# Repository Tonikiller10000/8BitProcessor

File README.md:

# 8Bit Computer

### Description:
This is a series of modules(3 at the moment) witch make an functional 8 bit processor for educational purposes: 
- [ALU](https://github.com/Tonikiller10000/8BitProcessor/tree/main/Processor_ALU_V1.0)
- [Display Register](https://github.com/Tonikiller10000/8BitProcessor/tree/main/DisplayRegister)
- [CLK Pulse Generator](https://github.com/Tonikiller10000/8BitProcessor/tree/main/ClkPulseGenerator)

> [!TIP]
> By clicking on a module link, you can read it\`s speciffic documentation.

<table>
  <tr>
    <td>ALU</td>
    <td>Display Register</td>
    <td>CLK Pulse Generator</td>
  </tr>
  <tr>
    <td></td>
    <td></td>
    <td></td>
  </tr>
 </table>

Links:
BenEater YouTube: https://www.youtube.com/beneater 
BenEater WebSite: https://eater.net/8bit   
GitHub: https://github.com/Tonikiller10000/8BitProcessor 
JLC: https://jlcpcb.com/ 

Photo:....

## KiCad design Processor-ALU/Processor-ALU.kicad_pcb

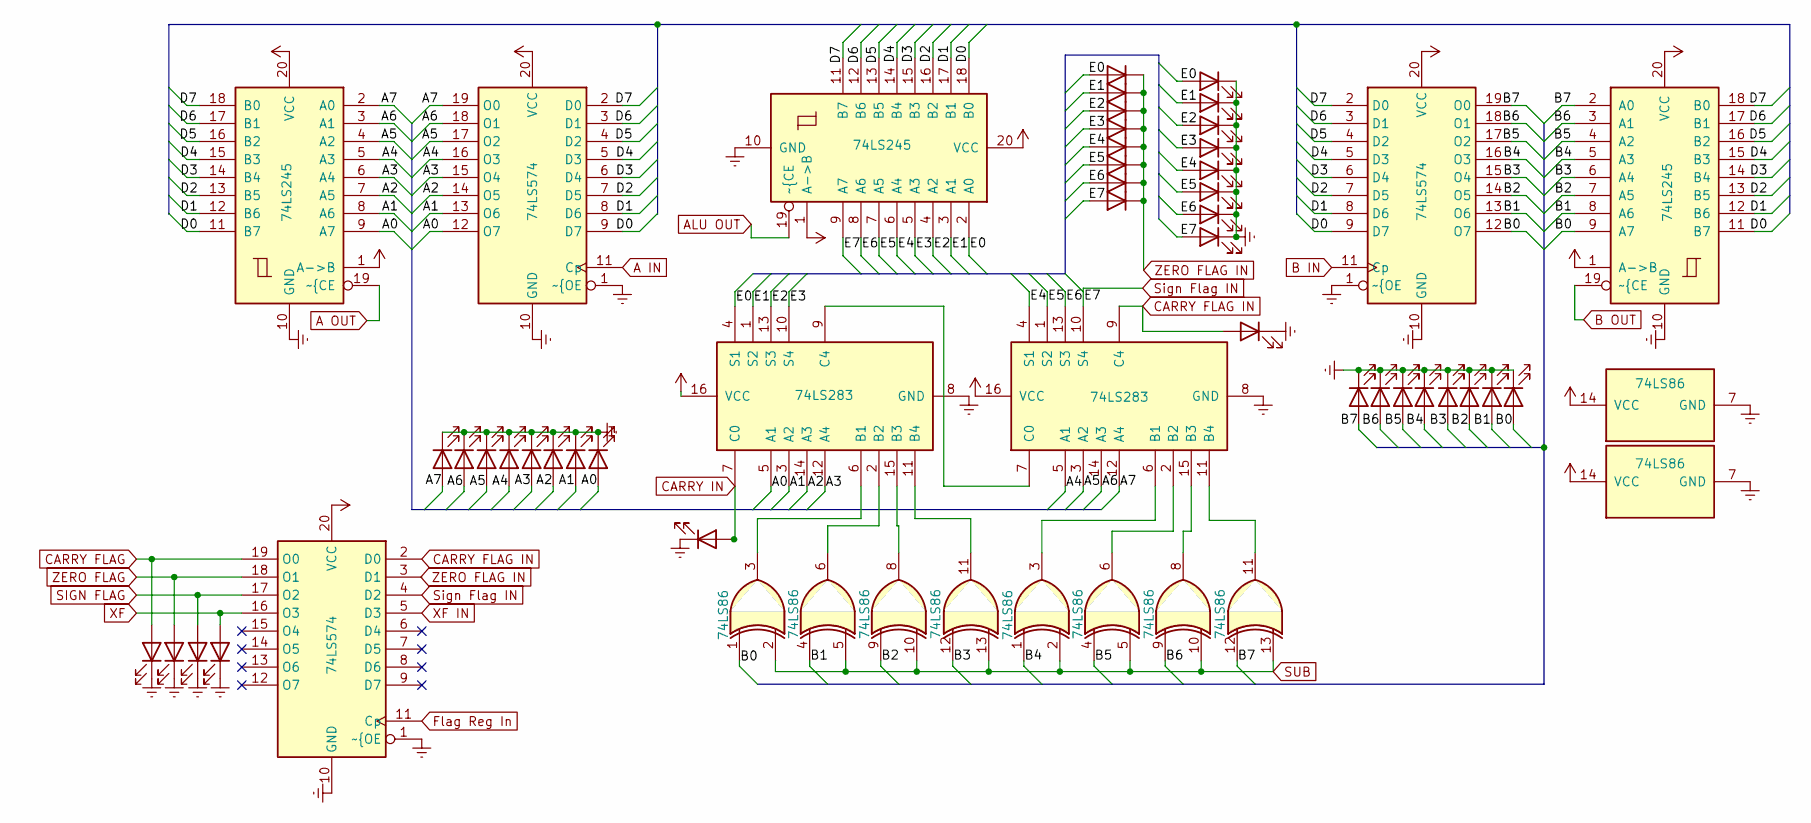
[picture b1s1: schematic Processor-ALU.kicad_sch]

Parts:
D1: C_{in}; LED_PLCC_2835
D2: XF; LED_PLCC_2835
D3: SF; LED_PLCC_2835
D4: ZF; LED_PLCC_2835
D5: CF; LED_PLCC_2835
D6, D10, D11, D12, D13, D14, D15, D17, D18, D34, D35, D36, D37, D38, D39, D40, D41, D42, D43, D44, D45, D46, D47, D48, D49: LED; LED_PLCC_2835
D16, D27, D28, D29, D30, D31, D32, D33: SK16; DIOM5027X250N
U1, U6, U10: 74LS245; DIP-20_W7.62mm_LongPads
U2, U3, U9: 74LS574; DIP-20_W7.62mm_LongPads
U4, U7: 74LS86; DIP-14_W7.62mm_LongPads
U5, U8: 74LS283; DIP-16_W7.62mm_LongPads

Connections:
/A0: D18.2 (A), U1.9 (A7), U3.12 (O7), U5.5 (A1)
/A1: D17.2 (A), U1.8 (A6), U3.13 (O6), U5.3 (A2)
/A2: D15.2 (A), U1.7 (A5), U3.14 (O5), U5.14 (A3)
/A3: D14.2 (A), U1.6 (A4), U3.15 (O4), U5.12 (A4)
/A4: D13.2 (A), U1.5 (A3), U3.16 (O3), U8.5 (A1)
/A5: D12.2 (A), U1.4 (A2), U3.17 (O2), U8.3 (A2)
/A6: D11.2 (A), U1.3 (A1), U3.18 (O1), U8.14 (A3)
/A7: D10.2 (A), U1.2 (A0), U3.19 (O0), U8.12 (A4)
/B0: D49.2 (A), U4.1, U9.12 (O7), U10.9 (A7)
/B1: D48.2 (A), U4.4, U9.13 (O6), U10.8 (A6)
/B2: D47.2 (A), U4.9, U9.14 (O5), U10.7 (A5)
/B3: D46.2 (A), U4.12, U9.15 (O4), U10.6 (A4)
/B4: D45.2 (A), U7.1, U9.16 (O3), U10.5 (A3)
/B5: D44.2 (A), U7.4, U9.17 (O2), U10.4 (A2)
/B6: D43.2 (A), U7.9, U9.18 (O1), U10.3 (A1)
/B7: D42.2 (A), U7.12, U9.19 (O0), U10.2 (A0)
/D0: U1.11 (B7), U3.9 (D7), U6.18 (B0), U9.9 (D7), U10.11 (B7); also elsewhere on the board
/D1: U1.12 (B6), U3.8 (D6), U6.17 (B1), U9.8 (D6), U10.12 (B6); also elsewhere on the board
/D2: U1.13 (B5), U3.7 (D5), U6.16 (B2), U9.7 (D5), U10.13 (B5); also elsewhere on the board
/D3: U1.14 (B4), U3.6 (D4), U6.15 (B3), U9.6 (D4), U10.14 (B4); also elsewhere on the board
/D4: U1.15 (B3), U3.5 (D3), U6.14 (B4), U9.5 (D3), U10.15 (B3); also elsewhere on the board
/D5: U1.16 (B2), U3.4 (D2), U6.13 (B5), U9.4 (D2), U10.16 (B2); also elsewhere on the board
/D6: U1.17 (B1), U3.3 (D1), U6.12 (B6), U9.3 (D1), U10.17 (B1); also elsewhere on the board
/D7: U1.18 (B0), U3.2 (D0), U6.11 (B7), U9.2 (D0), U10.18 (B0); also elsewhere on the board
/E0: D27.1 (A), D34.2 (A), U5.4 (S1), U6.2 (A0)
/E1: D28.1 (A), D35.2 (A), U5.1 (S2), U6.3 (A1)
/E2: D29.1 (A), D36.2 (A), U5.13 (S3), U6.4 (A2)
/E3: D30.1 (A), D37.2 (A), U5.10 (S4), U6.5 (A3)
/E4: D31.1 (A), D38.2 (A), U6.6 (A4), U8.4 (S1)
/E5: D32.1 (A), D39.2 (A), U6.7 (A5), U8.1 (S2)
/E6: D33.1 (A), D40.2 (A), U6.8 (A6), U8.13 (S3)
A IN: U3.11 (Cp); also elsewhere on the board
A OUT: U1.19 (~{CE); also elsewhere on the board
ALU OUT: U6.19 (~{CE); also elsewhere on the board
B IN: U9.11 (Cp); also elsewhere on the board
B OUT: U10.19 (~{CE); also elsewhere on the board
CARRY FLAG: D2.2 (A), U2.19 (O0); also elsewhere on the board
CARRY FLAG IN: D6.2 (A), U2.2 (D0), U8.9 (C4); also elsewhere on the board
CARRY IN: D1.2 (A), U5.7 (C0); also elsewhere on the board
Earth: D1.1 (K), D2.1 (K), D3.1 (K), D4.1 (K), D5.1 (K), D6.1 (K), D10.1 (K), D11.1 (K), D12.1 (K), D13.1 (K), D14.1 (K), D15.1 (K), D17.1 (K), D18.1 (K), D34.1 (K), D35.1 (K), D36.1 (K), D37.1 (K), D38.1 (K), D39.1 (K), D40.1 (K), D41.1 (K), D42.1 (K), D43.1 (K), D44.1 (K), D45.1 (K), D46.1 (K), D47.1 (K), D48.1 (K), D49.1 (K), U1.10 (GND), U2.1 (~{OE), U2.10 (GND), U3.1 (~{OE), U3.10 (GND), U4.7 (GND), U5.8 (GND), U6.10 (GND), U7.7 (GND), U8.8 (GND), U9.1 (~{OE), U9.10 (GND), U10.10 (GND); also elsewhere on the board
Flag Reg In: U2.11 (Cp); also elsewhere on the board
unnamed: U4.3, U5.6 (B1)
unnamed: U4.6, U5.2 (B2)
unnamed: U4.8, U5.15 (B3)
unnamed: U4.11, U5.11 (B4)
unnamed: U5.9 (C4), U8.7 (C0)
unnamed: U7.3, U8.6 (B1)
unnamed: U7.6, U8.2 (B2)
unnamed: U7.8, U8.15 (B3)
unnamed: U7.11, U8.11 (B4)
SIGN FLAG: D4.2 (A), U2.17 (O2); also elsewhere on the board
SUB: U4.2, U4.5, U4.10, U4.13, U7.2, U7.5, U7.10, U7.13; also elsewhere on the board
Sign Flag IN: D16.1 (A), D41.2 (A), U2.4 (D2), U6.9 (A7), U8.10 (S4); also elsewhere on the board
VCC: U1.1 (A->B), U1.20 (VCC), U2.20 (VCC), U3.20 (VCC), U4.14 (VCC), U5.16 (VCC), U6.1 (A->B), U6.20 (VCC), U7.14 (VCC), U8.16 (VCC), U9.20 (VCC), U10.1 (A->B), U10.20 (VCC); also elsewhere on the board
XF: D5.2 (A), U2.16 (O3); also elsewhere on the board
XF IN: U2.5 (D3); also elsewhere on the board
ZERO FLAG: D3.2 (A), U2.18 (O1); also elsewhere on the board
ZERO FLAG IN: D16.2 (K), D27.2 (K), D28.2 (K), D29.2 (K), D30.2 (K), D31.2 (K), D32.2 (K), D33.2 (K), U2.3 (D1); also elsewhere on the board

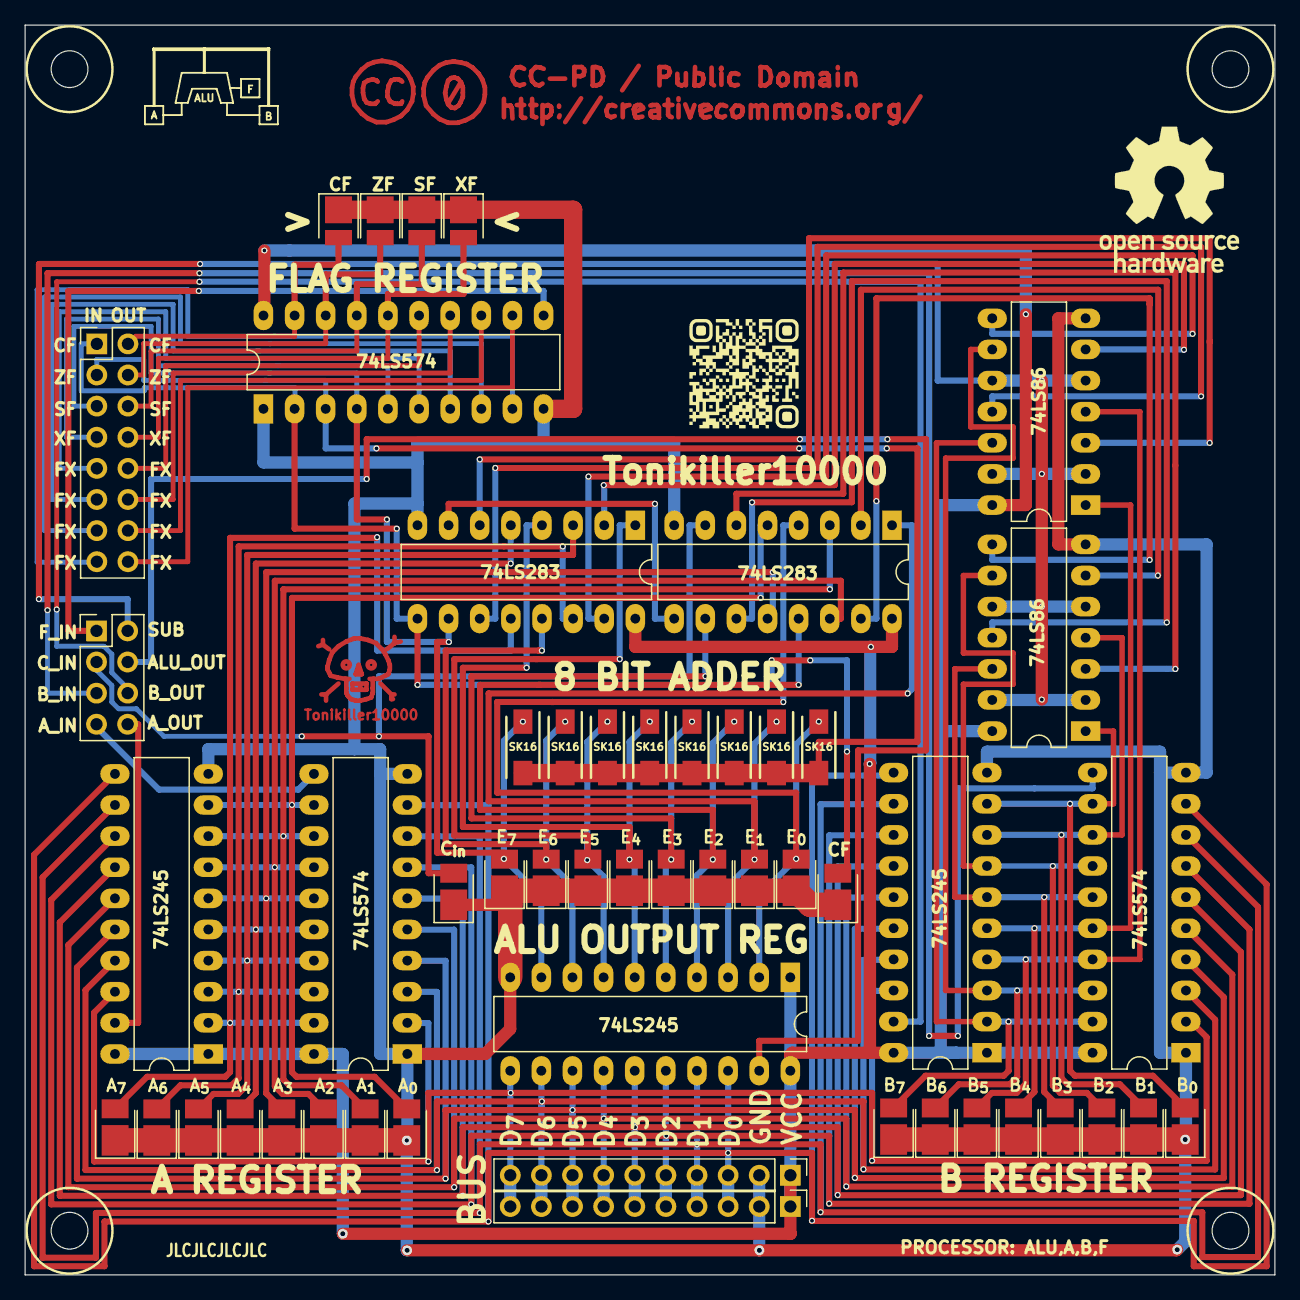
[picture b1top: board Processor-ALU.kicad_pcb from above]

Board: 2 copper layers, 102.0 x 102.0 mm, 52 parts (0 on the bottom side), 58 nets.

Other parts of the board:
P1: PinHeader_2x04_P2.54mm_Vertical
P2, P3: PinHeader_1x10_P2.54mm_Vertical
P4: Flag Reg; PinHeader_2x08_P2.54mm_Vertical

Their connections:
/D0: P2.3, P3.3; also elsewhere on the board
/D1: P2.4, P3.4; also elsewhere on the board
/D2: P2.5, P3.5; also elsewhere on the board
/D3: P2.6, P3.6; also elsewhere on the board
/D4: P2.7, P3.7; also elsewhere on the board
/D5: P2.8, P3.8; also elsewhere on the board
/D6: P2.9, P3.9; also elsewhere on the board
/D7: P2.10, P3.10; also elsewhere on the board
A IN: P1.7; also elsewhere on the board
A OUT: P1.8; also elsewhere on the board
ALU OUT: P1.4; also elsewhere on the board
B IN: P1.5; also elsewhere on the board
B OUT: P1.6; also elsewhere on the board
CARRY FLAG: P4.2; also elsewhere on the board
CARRY FLAG IN: P4.1; also elsewhere on the board
CARRY IN: P1.3; also elsewhere on the board
Earth: P2.2, P3.2; also elsewhere on the board
Flag Reg In: P1.1; also elsewhere on the board
SIGN FLAG: P4.6; also elsewhere on the board
SUB: P1.2; also elsewhere on the board
Sign Flag IN: P4.5; also elsewhere on the board
VCC: P2.1, P3.1; also elsewhere on the board
XF: P4.8; also elsewhere on the board
XF IN: P4.7; also elsewhere on the board
ZERO FLAG: P4.4; also elsewhere on the board
ZERO FLAG IN: P4.3; also elsewhere on the board

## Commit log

2023-09-09 8BitProcessor_Update1
    uploading files
2023-09-09 update2
    uploading files
2023-09-09 FirstCompleteUpdate
    All the starting files has been updated.
2024-02-09 Update1
